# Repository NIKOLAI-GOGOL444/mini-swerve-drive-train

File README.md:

IMPORTANT NOTE FOR OUTPOST REVIEWERS: please ignore the pcb stuff in my BOM.CSV and files and stuff. I do not have a pcb design yet, so I will not be requesting funding for that part of this project, and will request for it as a sepreate project at a later time. 
NEW NOTE: I have edited the BOM.csv file to exclude pcb stuff. 

IMPORTANT NOTE FOR HORIZONS REVIEWERS:
NOTE: i am ONLY trying to submit the CONTROLLER pcb right now. all my hours have been working on that, do not reject my project under the robot pcb stuff not being in here, thats because it isnt finished yet, ill submit that at a later date, just worry about the controller stuff. 
UPDATE: as of tuesday july 28 1:18 am, I have finished the controller pcb and uploaded the final designs file to the repo. it is now ready to be purchased.

8/31/26 UPDATE
after more work, I have resubmitted for hour aproval. since my last update to this repo, I have ordered my finished boards for manufacturing and recieved them in the mail. here are some images. I have begun assembly, first by harvesting some chips from old devboards and breakout modules. after that I hit a wall when I realized that salvaging tiny capacitors and resistors would be impossible, so now I am working on getting all my parts ordered so I can assemble. hopefully I get my hours aprovved soon so I can buy digikey grants, because that would seriously help me greatly. 

UPDATE: as of monday july 27th 11:36 pm, I have uploaded new gerbers that are of the pcb fully routed and corrected against the DRC. if wanted, the pcb could now be purchased and it would function, but the silkscreen labels would be a mess. im now going to arrange the silkscreen, then begin on the swerve drive brain pcb. 
NEW NOTE AFTER SECOND REJECTION: 
my pcb wasnt routed yet because this project is currently a work in progress. I am submitting it fairly early on because I want to qualify intime to go to horizons polaris (I have an extension to qualify until july 31st.) I have done work on my pcb and almost finished the routing, it is pretty close to done, just gotta double check everything and fix some small issues. just please understand that this pcb and its gerber files arent finsished, which explains the missing routing and anything you may find in this file. I am actively working on this project, so please give me grace with any structural errors that may be in the pcb and help me make the polaris deadline. im attaching the newer gerbers. 
my project for horizons is the pcbs that go with this robot, I am submitting them as a seperate hardware project that I will not need funding for. I am documenting my hours for the pcbs seperate from the code file I used on the robots cad and coding, however I will be using the same github for both projects just to keep things simple. so ignore all the cad and code stuff, and just look at the PCB stuff, because thats my horizons project. I am currently in the process of tracing the controller PCB, so all I have right now as I submit is the schematic and maybe a unfinished gerber file, but I will keep working on the project and add to my repo as I go. if you have any questions just reach me on the hackclub slack. 
ALSO, the BOM.CSV you see when you open my repo isnt the one for this project, that is for my outpost project. please look in my controller pcb stuff file, you will find my horizons BOM.CSV file in there. 
STEPS TO REPRODUCE:
when pcbs are finished, someone can recreate my PCBS by going online to a pcb manufacturing website, uploading the gerber files for my controller and robot control board I will eventually put in my repo, and ordering them, then either choosing to assemble the pcbs themselves or buying it preassembled. if they wanted recreate the FULL ROBOT (NOT INCLUDED WITH MY HORIZONS SUBMISSION, INCLUDING FYI) they would then flash the code in my repo to their PCBs, then 3d print the cad files with either their own 3d printer or through a manufacturing sight, assembling based off of the cad images ive attached for the project (i think I will add an assembly tutorial eventually), then plugging in batteries and then they would have my robot! 
NEWER 3D RENDERS AND PCB EDITOR SCREENSHOTS AS OF SUN JUL 26 2026

3D RENDERS (PLEASE NOTE THAT THE CONTROLLER PCB ISNT FINISHED, AND I HAVENT STARTED THE ROBOT PCB.[swervecontrollerPCBv1.pdf](https://github.com/user-attachments/files/30342656/swervecontrollerPCBv1.pdf)

hi!

im making a mini swerve drive train inspired by FRC swerve drive trains, because they just make me so happy lol.
if you cant tell already idk how to use github at all.
I hope to figure it out as I work on this project. 
if you need anything or have any questions about my project, id be happy to help! just contact me however that works on git idk.

thank you for your time,
-NIKOLAI!
# Mini Swerve Drive Train

inspired by my love of FRC swerve modules and drive trains, they're so freaking cool. 
this project is documented on forge, stardance, and horizons. 
I would most reccomend checking out stardance, because that is where this project is most actively docdumented. 
https://stardance.hackclub.com/projects/25609
ive logged around 25 hours as I write this, however I only began logging maybe two weeks ago, and in reality this project has taken MUCH much longer than that lol. 

AI declaration for hackclub

I worked with claude to turn my google docs parts list into a BOM.CSV file. I also use gemini or other chatbots to help me write code and understand data protocols. I never copy and paste exactly what is given to me without understanding what it is or why, but instead use AI as a learning tool to help me better learn and understand programming. especially as a new programmer, I am entirely self taught using online resources, and AI has been a very useful tool for my learning. 

here is a 3d demo of my cad, stl files are available in this repository. 

https://a360.co/4gOPGcb

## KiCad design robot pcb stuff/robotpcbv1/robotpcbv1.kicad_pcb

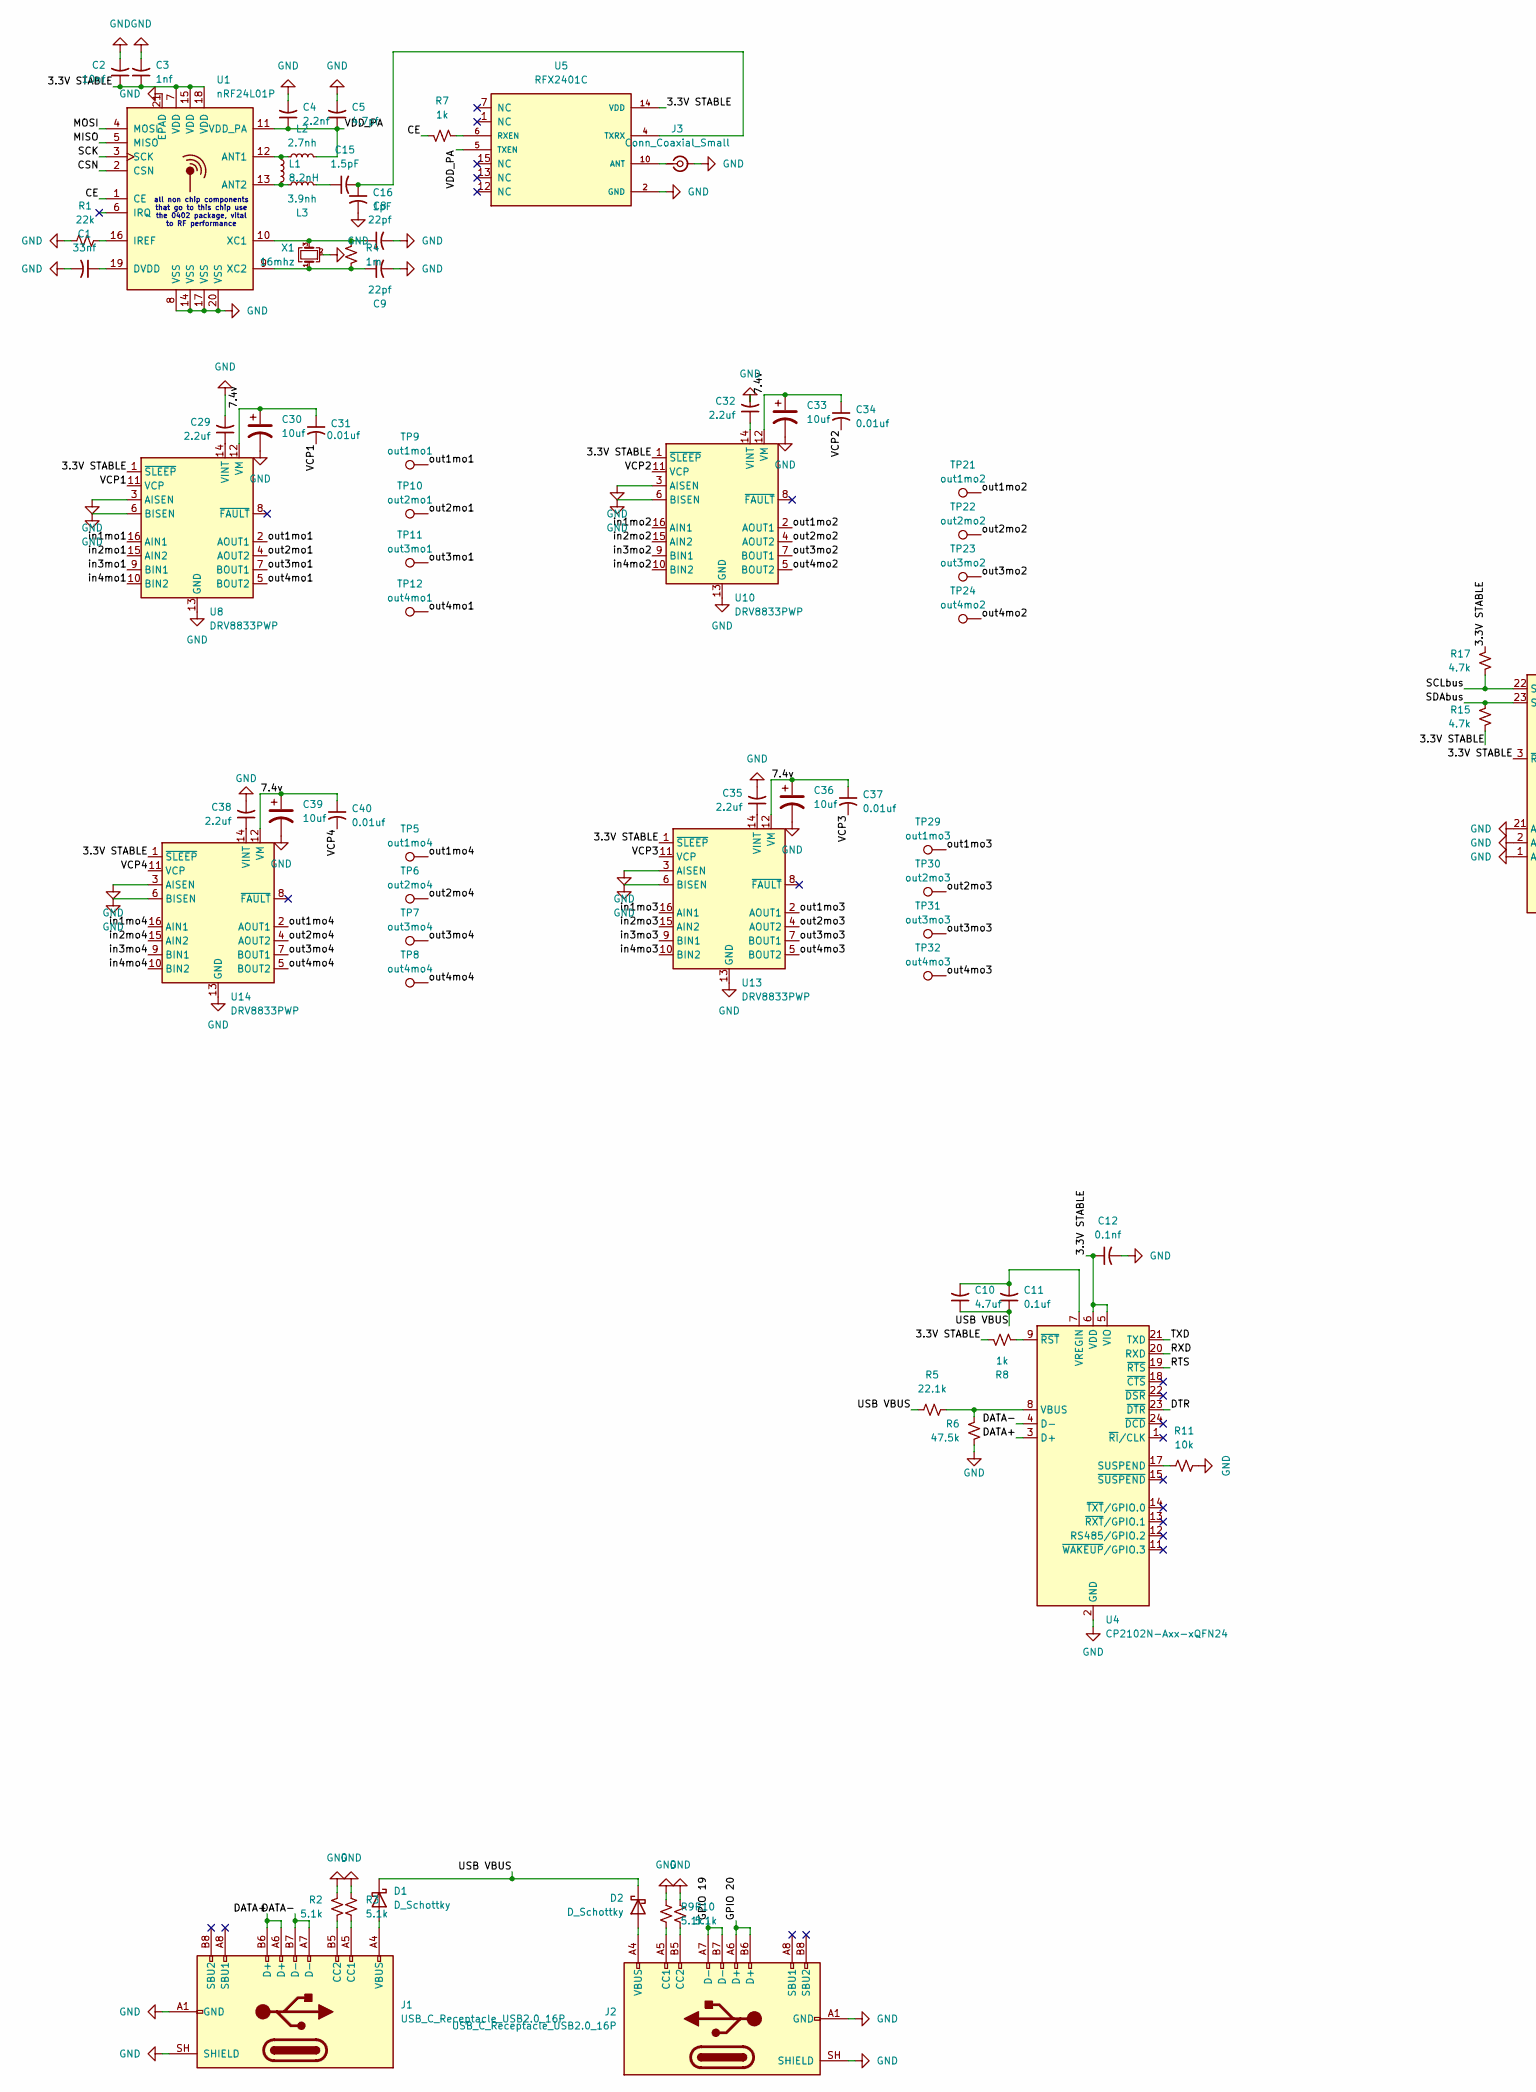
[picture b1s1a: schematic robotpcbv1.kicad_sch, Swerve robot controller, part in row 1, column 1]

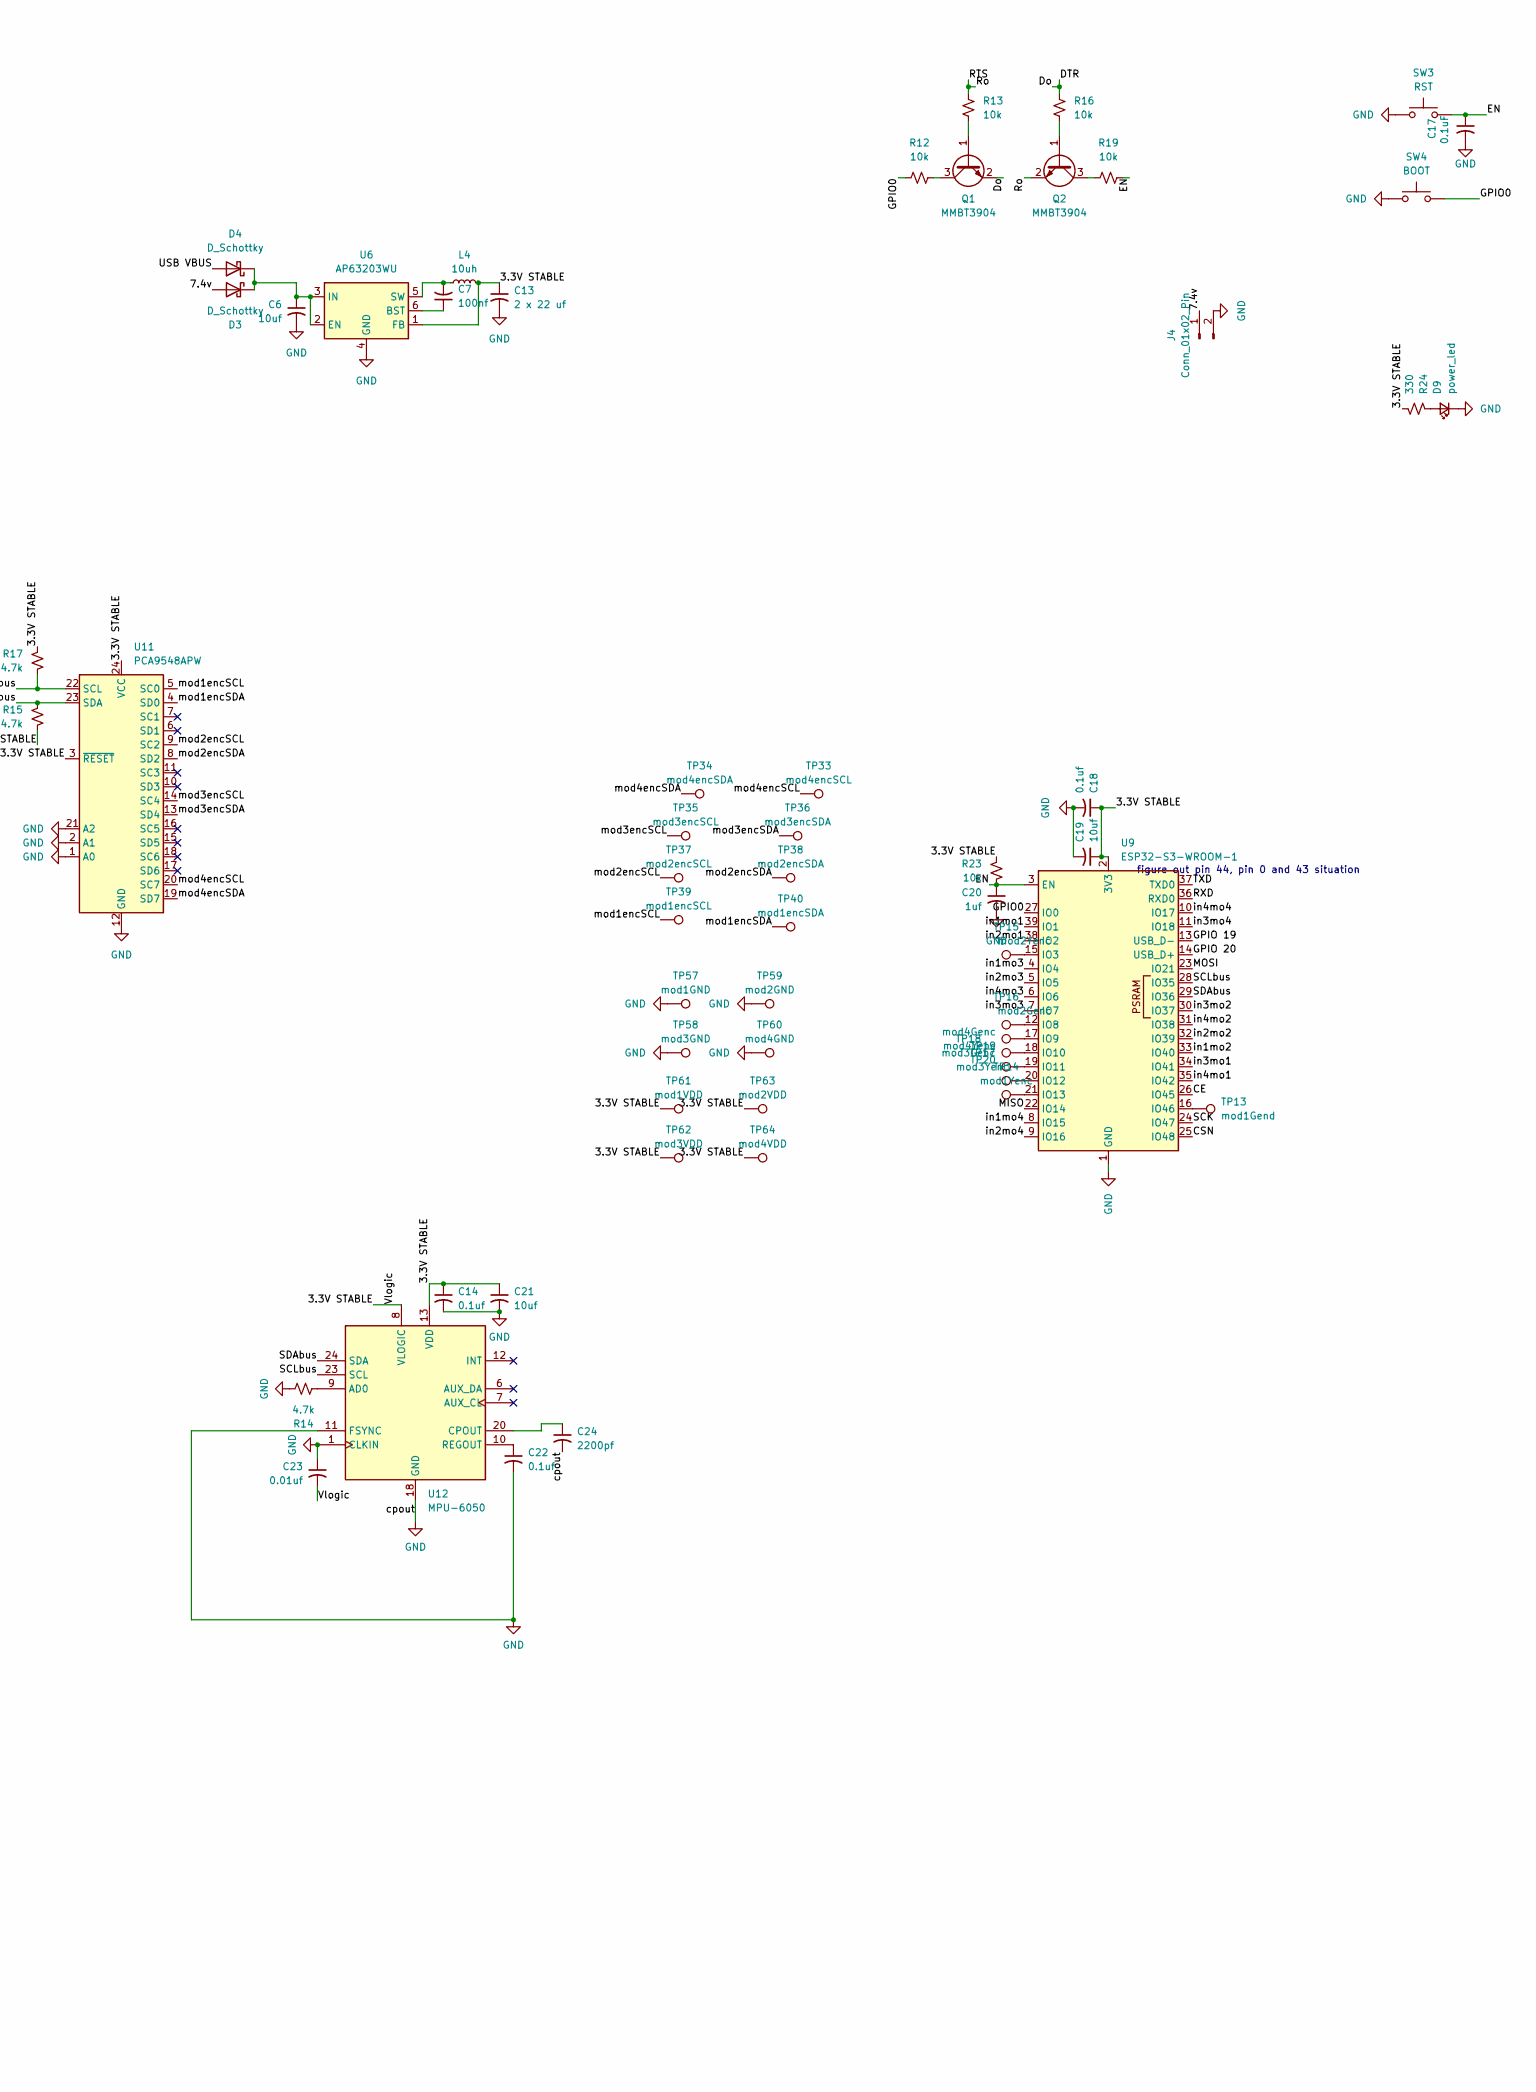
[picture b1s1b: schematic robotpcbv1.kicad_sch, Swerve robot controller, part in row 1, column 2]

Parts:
C1: 33nf; C_0402_1005Metric
C2: 10nf; C_0402_1005Metric
C3: 1nf; C_0402_1005Metric
C4: 2.2nf; C_0402_1005Metric
C5: 4.7pf; C_0402_1005Metric
C6, C19, C21: 10uf; C_1206_3216Metric
C7: 100nf; C_0402_1005Metric
C8, C9: 22pf; C_0402_1005Metric
C10: 4.7uf; C_1206_3216Metric
C11, C14, C18, C22: 0.1uf; C_0603_1608Metric
C12: 0.1nf; C_0603_1608Metric
C13: 2 x 22 uf; C_0805_2012Metric
C15: 1.5pF; C_0402_1005Metric
C16: 1pF; C_0402_1005Metric
C17: 0.1uF; C_0603_1608Metric
C20: 1uf; C_1206_3216Metric
C23, C31, C34, C37, C40: 0.01uf; C_0402_1005Metric
C24: 2200pf; C_0402_1005Metric
C29, C32, C35, C38: 2.2uf; C_0603_1608Metric
C30, C33, C36, C39: 10uf; C_0805_2012Metric
D1, D2, D3, D4: D_Schottky; D_SOD-123
D9: power_led; LED_0603_1608Metric
J1, J2: USB_C_Receptacle_USB2.0_16P; USB_C_Receptacle_HRO_TYPE-C-31-M-12
J3: Conn_Coaxial_Small; SMA_Amphenol_901-144_Vertical
J4: Conn_01x02_Pin; AMASS_XT60-M_1x02_P7.20mm_Vertical
L1: 8.2nH; L_0402_1005Metric
L2: 2.7nh; L_0402_1005Metric
L3: 3.9nh; L_0402_1005Metric
L4: 10uh; WE-LQSA_5040
Q1, Q2: MMBT3904; SOT-23
R1: 22k; R_0603_1608Metric
R2, R3, R9, R10: 5.1k; R_0603_1608Metric
R4: 1m; R_0603_1608Metric
R5: 22.1k; R_0603_1608Metric
R6: 47.5k; R_0603_1608Metric
R7, R8: 1k; R_0603_1608Metric
R11, R12, R13, R16, R19, R23: 10k; R_0603_1608Metric
R14, R15, R17: 4.7k; R_0603_1608Metric
R24: 330; R_0603_1608Metric
SW3: RST; SW_Push_SPST_NO_Alps_SKRK
SW4: BOOT; SW_Push_SPST_NO_Alps_SKRK
TP5: out1mo4; TestPoint_Pad_D1.0mm
TP6: out2mo4; TestPoint_Pad_D1.0mm
TP7: out3mo4; TestPoint_Pad_D1.0mm
TP8: out4mo4; TestPoint_Pad_D1.0mm
TP9: out1mo1; TestPoint_Pad_D1.0mm
TP10: out2mo1; TestPoint_Pad_D1.0mm
TP11: out3mo1; TestPoint_Pad_D1.0mm
TP12: out4mo1; TestPoint_Pad_D1.0mm
TP13: mod1Gend; TestPoint_Pad_D1.0mm
TP14: mod1Yenc; TestPoint_Pad_D1.0mm
TP15: mod2Yenc; TestPoint_Pad_D1.0mm
TP16: mod2Genc; TestPoint_Pad_D1.0mm
TP17: mod3Yenc; TestPoint_Pad_D1.0mm
TP18: mod3Genc; TestPoint_Pad_D1.0mm
TP19: mod4Genc; TestPoint_Pad_D1.0mm
TP20: mod4Yenc; TestPoint_Pad_D1.0mm
TP21: out1mo2; TestPoint_Pad_D1.0mm
TP22: out2mo2; TestPoint_Pad_D1.0mm
TP23: out3mo2; TestPoint_Pad_D1.0mm
TP24: out4mo2; TestPoint_Pad_D1.0mm
TP29: out1mo3; TestPoint_Pad_D1.0mm
TP30: out2mo3; TestPoint_Pad_D1.0mm
TP31: out3mo3; TestPoint_Pad_D1.0mm
TP32: out4mo3; TestPoint_Pad_D1.0mm
TP33: mod4encSCL; TestPoint_Pad_D1.0mm
TP34: mod4encSDA; TestPoint_Pad_D1.0mm
TP35: mod3encSCL; TestPoint_Pad_D1.0mm
TP36: mod3encSDA; TestPoint_Pad_D1.0mm
TP37: mod2encSCL; TestPoint_Pad_D1.0mm
TP38: mod2encSDA; TestPoint_Pad_D1.0mm
TP39: mod1encSCL; TestPoint_Pad_D1.0mm
TP40: mod1encSDA; TestPoint_Pad_D1.0mm
TP57: mod1GND; TestPoint_Pad_D1.0mm
TP58: mod3GND; TestPoint_Pad_D1.0mm
TP59: mod2GND; TestPoint_Pad_D1.0mm
TP60: mod4GND; TestPoint_Pad_D1.0mm
TP61: mod1VDD; TestPoint_Pad_D1.0mm
TP62: mod3VDD; TestPoint_Pad_D1.0mm
TP63: mod2VDD; TestPoint_Pad_D1.0mm
TP64: mod4VDD; TestPoint_Pad_D1.0mm
U1: nRF24L01P; QFN-20-1EP_4x4mm_P0.5mm_EP2.5x2.5mm
U4: CP2102N-Axx-xQFN24; QFN-24-1EP_4x4mm_P0.5mm_EP2.6x2.6mm
U5: RFX2401C; QFN50P300X300X60-17N; DigiKey_Part_Number 863-1828-1-ND
U6: AP63203WU; TSOT-23-6
U8, U10, U13, U14: DRV8833PWP; HTSSOP-16-1EP_4.4x5mm_P0.65mm_EP3.4x5mm_Mask2.46x2.31mm_The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
U9: ESP32-S3-WROOM-1; ESP32-S3-WROOM-1U
U11: PCA9548APW; TSSOP-24_4.4x7.8mm_P0.65mm
U12: MPU-6050; InvenSense_QFN-24_4x4mm_P0.5mm
X1: 16mhz; Crystal_SMD_3225-4Pin_3.2x2.5mm

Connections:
/7.4v: C30.1, C31.1, C33.1, C34.1, C36.1, C37.1, C39.1, C40.1, D3.2 (A), J4.1, U8.12 (VM), U10.12 (VM), U13.12 (VM), U14.12 (VM)
/CE: R7.2, U1.1 (CE), U9.26 (IO45)
/CSN: U1.2 (CSN), U9.25 (IO48)
/DATA+: J1.A6 (D+), J1.B6 (D+), U4.3 (D+)
/DATA-: J1.A7 (D-), J1.B7 (D-), U4.4 (D-)
/DTR: Q1.2 (E), R16.1, U4.23 (~DTR)
/EN: C17.1, C20.1, R19.1, R23.1, SW3.2, U9.3 (EN)
/GPIO0: R12.2, SW4.2, U9.27 (IO0)
/GPIO 19: J2.A7 (D-), J2.B7 (D-), U9.13 (USB_D-)
/GPIO 20: J2.A6 (D+), J2.B6 (D+), U9.14 (USB_D+)
/MISO: U1.5 (MISO), U9.22 (IO14)
/MOSI: U1.4 (MOSI), U9.23 (IO21)
/RTS: Q2.2 (E), R13.1, U4.19 (~RTS)
/RXD: U4.20 (RXD), U9.36 (RXD0)
/SCK: U1.3 (SCK), U9.24 (IO47)
/SCLbus: R17.2, U9.28 (IO35), U11.22 (SCL), U12.23 (SCL)
/SDAbus: R15.1, U9.29 (IO36), U11.23 (SDA), U12.24 (SDA)
/TXD: U4.21 (TXD), U9.37 (TXD0)
/USB VBUS: C10.1, C11.1, D1.1 (K), D2.1 (K), D4.2 (A), R5.1
/VCP1: C31.2, U8.11 (VCP)
/VCP2: C34.2, U10.11 (VCP)
/VCP3: C37.2, U13.11 (VCP)
/VCP4: C40.2, U14.11 (VCP)
/VDD_PA: C4.1, C5.1, L2.2, U1.11 (VDD_PA), U5.5 (TXEN)
/in1mo1: U8.16 (AIN1), U9.39 (IO1)
/in1mo2: U9.33 (IO40), U10.16 (AIN1)
/in1mo3: U9.4 (IO4), U13.16 (AIN1)
/in1mo4: U9.8 (IO15), U14.16 (AIN1)
/in2mo1: U8.15 (AIN2), U9.38 (IO2)
/in2mo2: U9.32 (IO39), U10.15 (AIN2)
/in2mo3: U9.5 (IO5), U13.15 (AIN2)
/in2mo4: U9.9 (IO16), U14.15 (AIN2)
/in3mo1: U8.9 (BIN1), U9.34 (IO41)
/in3mo2: U9.30 (IO37), U10.9 (BIN1)
/in3mo3: U9.7 (IO7), U13.9 (BIN1)
/in3mo4: U9.11 (IO18), U14.9 (BIN1)
/in4mo1: U8.10 (BIN2), U9.35 (IO42)
/in4mo2: U9.31 (IO38), U10.10 (BIN2)
/in4mo3: U9.6 (IO6), U13.10 (BIN2)
/in4mo4: U9.10 (IO17), U14.10 (BIN2)
/mod1encSCL: TP39.1 (1_1), U11.5 (SC0)
/mod1encSDA: TP40.1 (1_1), U11.4 (SD0)
/mod2encSCL: TP37.1 (1_1), U11.9 (SC2)
/mod2encSDA: TP38.1 (1_1), U11.8 (SD2)
/mod3encSCL: TP35.1 (1_1), U11.14 (SC4)
/mod3encSDA: TP36.1 (1_1), U11.13 (SD4)
/mod4encSCL: TP33.1 (1_1), U11.20 (SC7)
/mod4encSDA: TP34.1 (1_1), U11.19 (SD7)
/out1mo1: TP9.1 (1_1), U8.2 (AOUT1)
/out1mo2: TP21.1 (1_1), U10.2 (AOUT1)
/out1mo3: TP29.1 (1_1), U13.2 (AOUT1)
/out1mo4: TP5.1 (1_1), U14.2 (AOUT1)
/out2mo1: TP10.1 (1_1), U8.4 (AOUT2)
/out2mo2: TP22.1 (1_1), U10.4 (AOUT2)
/out2mo3: TP30.1 (1_1), U13.4 (AOUT2)
/out2mo4: TP6.1 (1_1), U14.4 (AOUT2)
/out3mo1: TP11.1 (1_1), U8.7 (BOUT1)
/out3mo2: TP23.1 (1_1), U10.7 (BOUT1)
/out3mo3: TP31.1 (1_1), U13.7 (BOUT1)
/out3mo4: TP7.1 (1_1), U14.7 (BOUT1)
/out4mo1: TP12.1 (1_1), U8.5 (BOUT2)
/out4mo2: TP24.1 (1_1), U10.5 (BOUT2)
/out4mo3: TP32.1 (1_1), U13.5 (BOUT2)
/out4mo4: TP8.1 (1_1), U14.5 (BOUT2)
GND: C1.2, C2.2, C3.2, C4.2, C5.2, C6.2, C8.2, C9.2, C12.2, C13.2, C14.2, C16.2, C17.2, C18.2, C19.2, C20.2, C21.2, C22.2, C23.1, C24.2, C29.2, C30.2, C32.2, C33.2, C35.2, C36.2, C38.2, C39.2, D9.1 (K), J1.A1 (GND), J1.A12 (GND), J1.B1 (GND), J1.B12 (GND), J1.SH (SHIELD), J2.A1 (GND), J2.A12 (GND), J2.B1 (GND), J2.B12 (GND), J2.SH (SHIELD), J3.2 (Ext), J4.2, R1.2, R2.1, R3.1, R6.2, R9.1, R10.1, R11.2, R14.2, SW3.1, SW4.1, TP57.1 (1_1), TP58.1 (1_1), TP59.1 (1_1), TP60.1 (1_1), U1.8 (VSS), U1.14 (VSS), U1.17 (VSS), U1.20 (VSS), U1.21 (EPAD), U4.2 (GND), U4.25 (GND), U5.2 (GND), U5.3 (GND), U5.8 (GND), U5.9 (GND), U5.11 (GND), U5.17 (GND), U6.4 (GND), U8.3 (AISEN), U8.6 (BISEN), U8.13 (GND), U8.17 (GND), U9.1 (GND), U9.40 (GND), U9.41 (GND), U10.3 (AISEN), U10.6 (BISEN), U10.13 (GND), U10.17 (GND), U11.1 (A0), U11.2 (A1), U11.12 (GND), U11.21 (A2), U12.1 (CLKIN), U12.11 (FSYNC), U12.18 (GND), U13.3 (AISEN), U13.6 (BISEN), U13.13 (GND), U13.17 (GND), U14.3 (AISEN), U14.6 (BISEN), U14.13 (GND), U14.17 (GND), X1.2 (G), X1.4 (G)
unnamed: C15.1, L3.1
unnamed: D1.2 (A), J1.A4 (VBUS), J1.A9 (VBUS), J1.B4 (VBUS), J1.B9 (VBUS)
unnamed: D2.2 (A), J2.A4 (VBUS), J2.A9 (VBUS), J2.B4 (VBUS), J2.B9 (VBUS)
unnamed: C6.1, D3.1 (K), D4.1 (K), U6.2 (EN), U6.3 (IN)
unnamed: D9.2 (A), R24.1
unnamed: J1.A5 (CC1), R3.2
unnamed: J1.B5 (CC2), R2.2
unnamed: J2.A5 (CC1), R9.2
unnamed: J2.B5 (CC2), R10.2
unnamed: J3.1 (In), U5.10 (ANT)
unnamed: Q1.1 (B), R13.2
unnamed: Q1.3 (C), R12.1
unnamed: Q2.1 (B), R16.2
unnamed: Q2.3 (C), R19.2
unnamed: L1.1, L2.1, U1.12 (ANT1)
unnamed: L1.2, L3.2, U1.13 (ANT2)
unnamed: C1.1, U1.19 (DVDD)
unnamed: R1.1, U1.16 (IREF)
unnamed: C8.1, R4.1, U1.10 (XC1), X1.3
unnamed: C9.1, R4.2, U1.9 (XC2), X1.1
unnamed: R11.1, U4.17 (SUSPEND)
unnamed: R5.2, R6.1, U4.8 (VBUS)
unnamed: C10.2, C11.2, U4.7 (VREGIN)
unnamed: R8.2, U4.9 (~RST)
unnamed: R7.1, U5.6 (RXEN)
unnamed: C15.2, C16.1, U5.4 (TXRX)
unnamed: C7.1, U6.6 (BST)
unnamed: C7.2, L4.1, U6.5 (SW)
unnamed: C29.1, U8.14 (VINT)
unnamed: TP15.1 (1_1), U9.15 (IO3)
unnamed: TP16.1 (1_1), U9.12 (IO8)
unnamed: TP19.1 (1_1), U9.17 (IO9)
unnamed: TP20.1 (1_1), U9.18 (IO10)
unnamed: TP18.1 (1_1), U9.19 (IO11)
unnamed: TP17.1 (1_1), U9.20 (IO12)
unnamed: TP14.1 (1_1), U9.21 (IO13)
unnamed: TP13.1 (1_1), U9.16 (IO46)
unnamed: C32.1, U10.14 (VINT)
unnamed: R14.1, U12.9 (AD0)
unnamed: C24.1, U12.20 (CPOUT)
unnamed: C22.1, U12.10 (REGOUT)
unnamed: C35.1, U13.14 (VINT)
unnamed: C38.1, U14.14 (VINT)
VDD: C2.1, C3.1, C12.1, C13.1, C14.1, C18.1, C19.1, C21.1, C23.2, L4.2, R8.1, R15.2, R17.1, R23.2, R24.2, TP61.1 (1_1), TP62.1 (1_1), TP63.1 (1_1), TP64.1 (1_1), U1.7 (VDD), U1.15 (VDD), U1.18 (VDD), U4.5 (VIO), U4.6 (VDD), U5.14 (VDD), U5.16 (VDD), U6.1 (FB), U8.1 (~SLEEP), U9.2 (3V3), U10.1 (~SLEEP), U11.3 (~RESET), U11.24 (VCC), U12.8 (VLOGIC), U12.13 (VDD), U13.1 (~SLEEP), U14.1 (~SLEEP)

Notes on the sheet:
figure out pin 44, pin 0 and 43 situation
all non chip components that go to this chip use the 0402 package, vital to RF performance

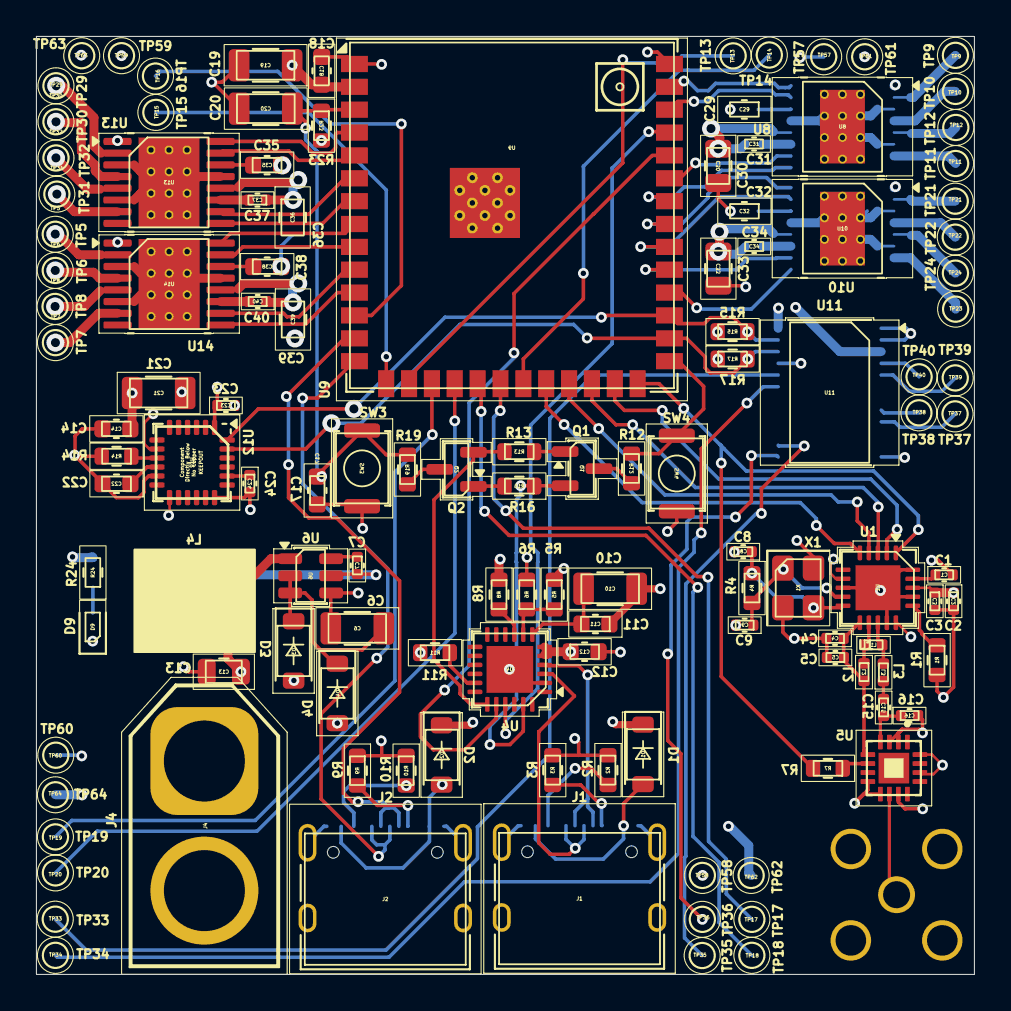
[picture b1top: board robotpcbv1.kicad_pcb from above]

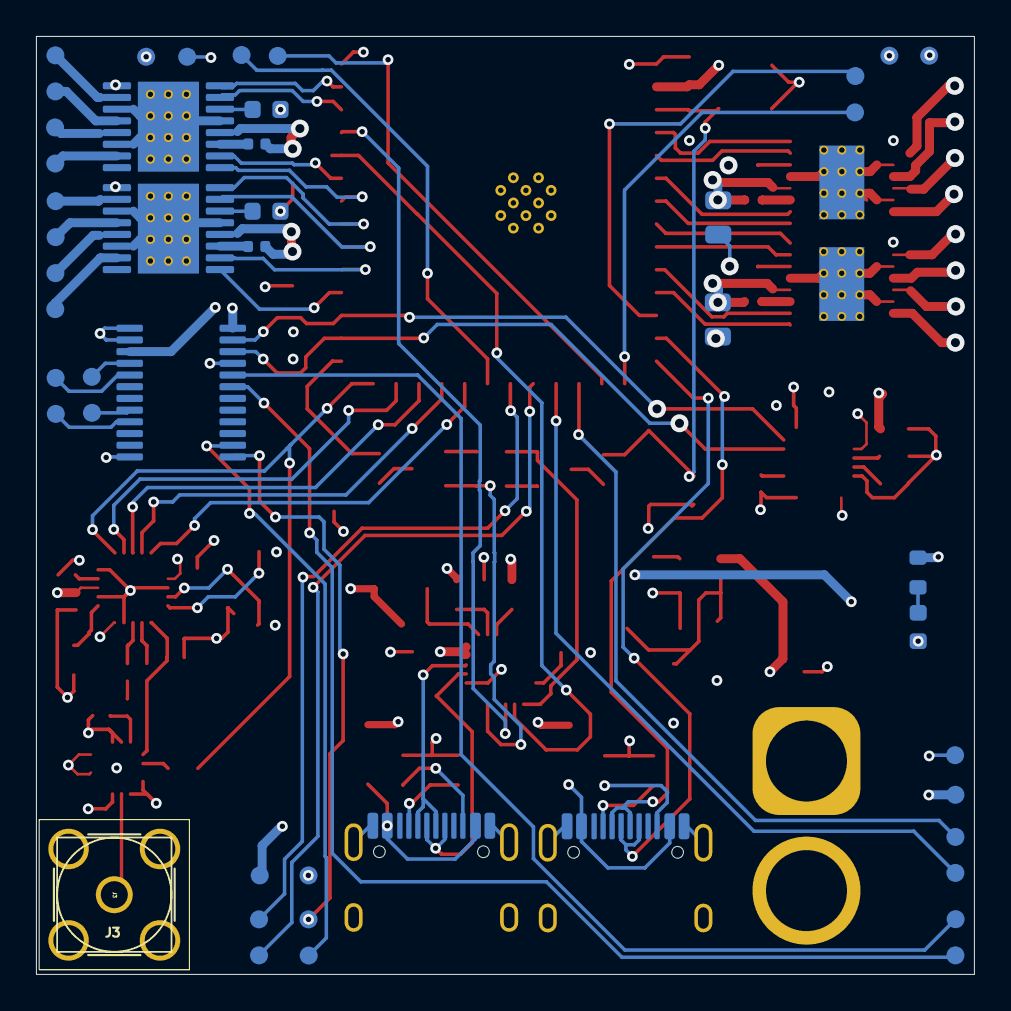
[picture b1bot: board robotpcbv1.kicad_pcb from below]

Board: 4 copper layers, 52.1 x 52.1 mm, 125 parts (54 on the bottom side), 109 nets.

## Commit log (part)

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2026-06-10 Add files via upload
    photos of the swerves. this is version 4, 5 is about the same, except the housing is much better, and the measuements on the swerves themselves are tweaked a little
2026-06-25 Add files via upload
    swerve module CAD v5, fixed gear meshing issues, and made a chasis!
